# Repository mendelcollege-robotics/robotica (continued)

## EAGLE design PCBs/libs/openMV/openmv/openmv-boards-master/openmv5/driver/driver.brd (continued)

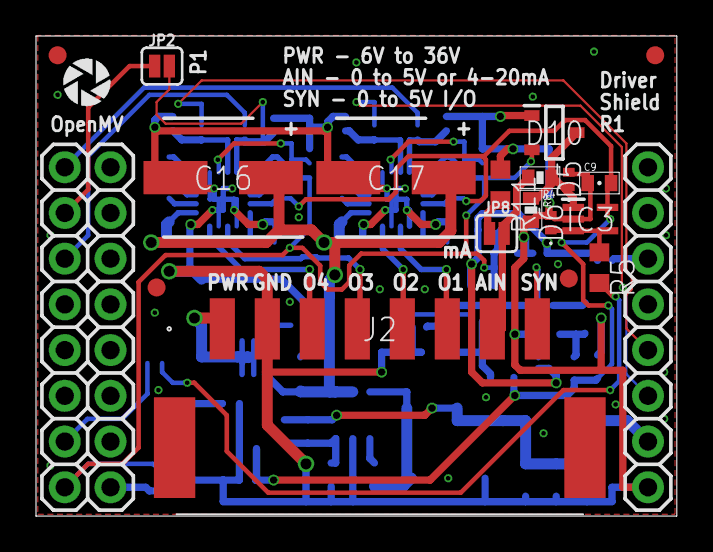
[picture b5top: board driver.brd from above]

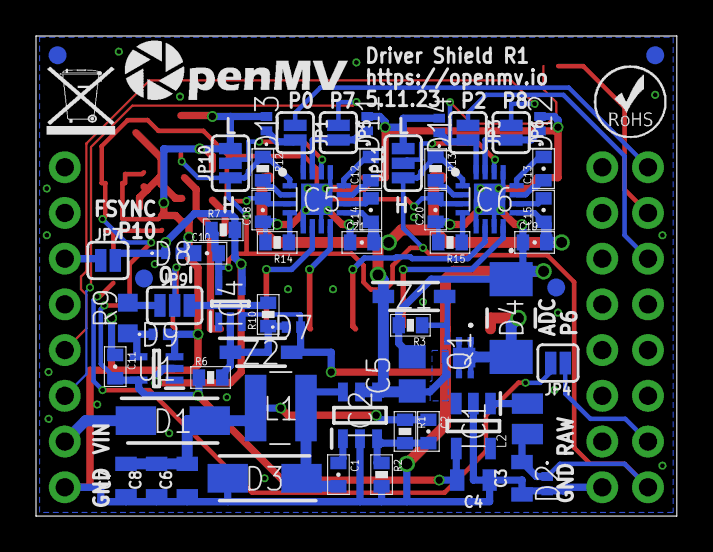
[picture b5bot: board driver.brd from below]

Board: 2 copper layers, 35.6 x 26.7 mm, 87 parts (67 on the bottom side), 50 nets.

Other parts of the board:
U$1: WEEE
U$2: ROHS
U$3: OMV-LOGO
U$9: OPENMV-LOGO

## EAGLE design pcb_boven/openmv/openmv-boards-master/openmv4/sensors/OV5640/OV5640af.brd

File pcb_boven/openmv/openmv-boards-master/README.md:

# OpenMV Boards

OpenMV boards, schematics, layouts, and CAD.

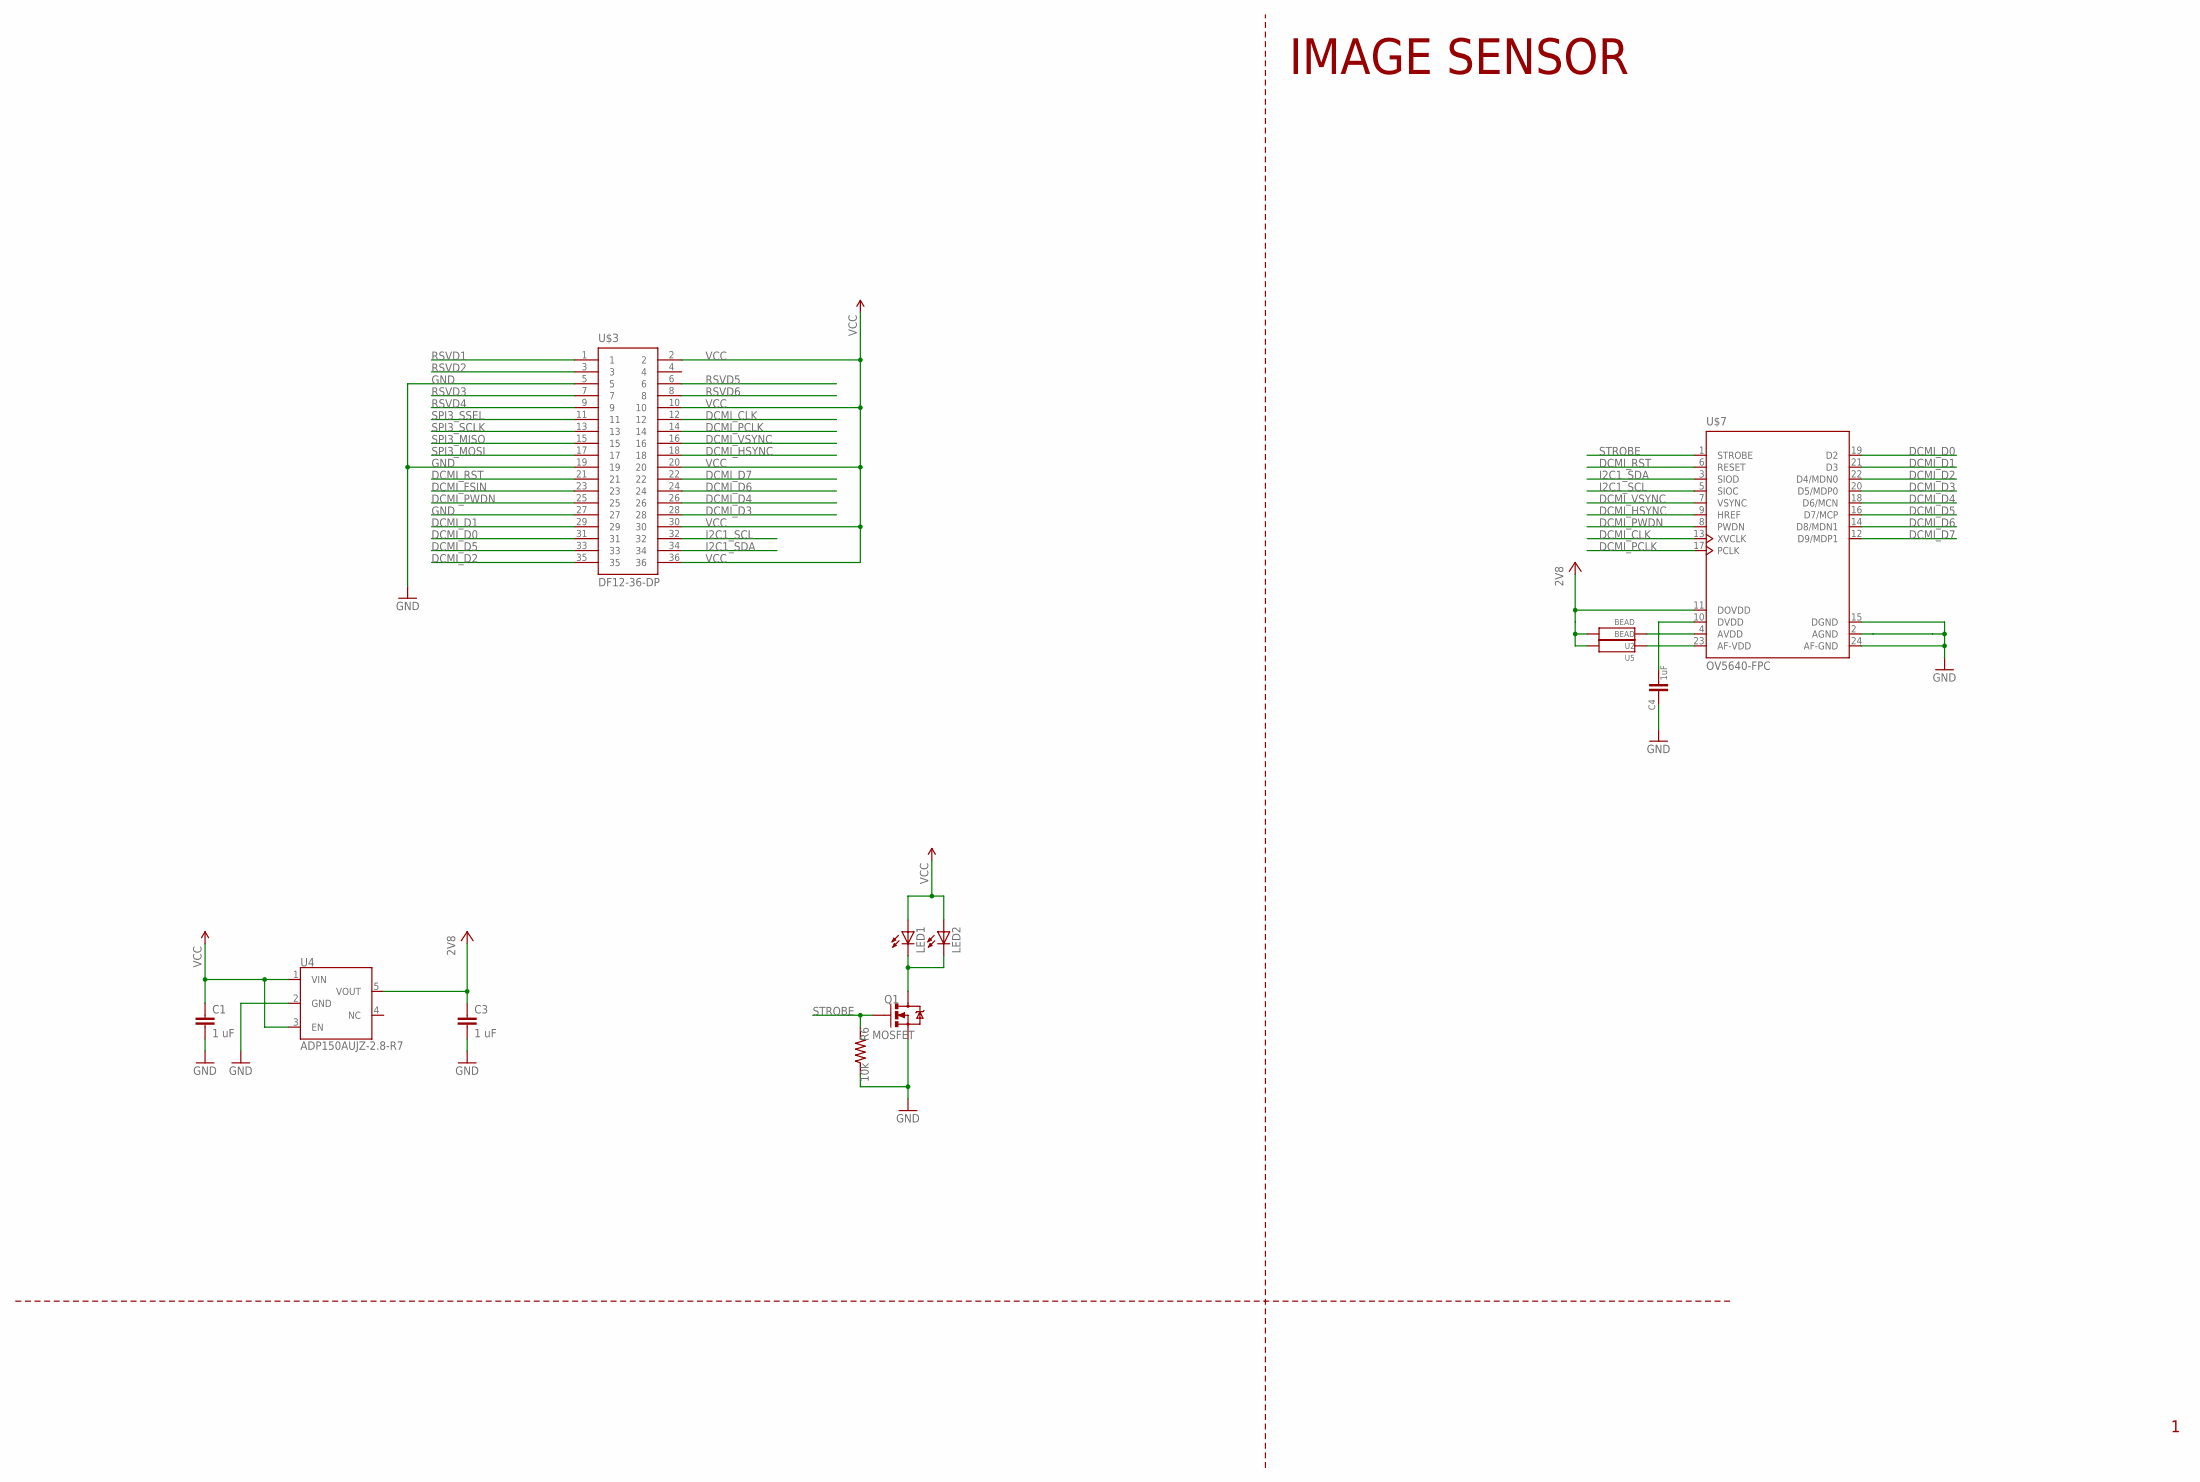
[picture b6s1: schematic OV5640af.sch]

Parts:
C1, C3: 1 uF; 0402-CAP
C4: 1uF; 0402-CAP
LED1, LED2: LEDCHIPLED_1206; CHIPLED_1206
Q1: MOSFET; SOT23-3
R6: 10k; 0603-RES
U2, U5: BEAD; 0402-CAP
U4: ADP150AUJZ-2.8-R7; SOT23-5
U$3: DF12-36-DP
U$7: OV5640-FPC; FPC24

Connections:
2V8: C3.1, U2.2, U4.5 (VOUT), U5.2, U$7.11 (DOVDD)
AF-VDD: U5.1, U$7.23 (AF-VDD)
AVDD: U2.1, U$7.4 (AVDD)
DCMI_CLK: U$3.12, U$7.13 (XVCLK)
DCMI_D0: U$3.31, U$7.19 (D2)
DCMI_D1: U$3.29, U$7.21 (D3)
DCMI_D2: U$3.35, U$7.22 (D4/MDN0)
DCMI_D3: U$3.28, U$7.20 (D5/MDP0)
DCMI_D4: U$3.26, U$7.18 (D6/MCN)
DCMI_D5: U$3.33, U$7.16 (D7/MCP)
DCMI_D6: U$3.24, U$7.14 (D8/MDN1)
DCMI_D7: U$3.22, U$7.12 (D9/MDP1)
DCMI_FSIN: U$3.23
DCMI_HSYNC: U$3.18, U$7.9 (HREF)
DCMI_PCLK: U$3.14, U$7.17 (PCLK)
DCMI_PWDN: U$3.25, U$7.8 (PWDN)
DCMI_RST: U$3.21, U$7.6 (RESET)
DCMI_VSYNC: U$3.16, U$7.7 (VSYNC)
DVDD: C4.1, U$7.10 (DVDD)
GND: C1.2, C3.2, C4.2, Q1.2 (S), R6.1, U4.2 (GND), U$3.5, U$3.19, U$3.27, U$7.2 (AGND), U$7.15 (DGND), U$7.24 (AF-GND)
I2C1_SCL: U$3.32, U$7.5 (SIOC)
I2C1_SDA: U$3.34, U$7.3 (SIOD)
LEDK: LED1.C, LED2.C, Q1.3 (D)
RSVD1: U$3.1
RSVD2: U$3.3
RSVD3: U$3.7
RSVD4: U$3.9
RSVD5: U$3.6
RSVD6: U$3.8
SPI3_MISO: U$3.15
SPI3_MOSI: U$3.17
SPI3_SCLK: U$3.13
SPI3_SSEL: U$3.11
STROBE: Q1.1 (G), R6.2, U$7.1 (STROBE)
VCC: C1.1, LED1.A, LED2.A, U4.1 (VIN), U4.3 (EN), U$3.2, U$3.10, U$3.20, U$3.30, U$3.36

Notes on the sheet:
IMAGE SENSOR

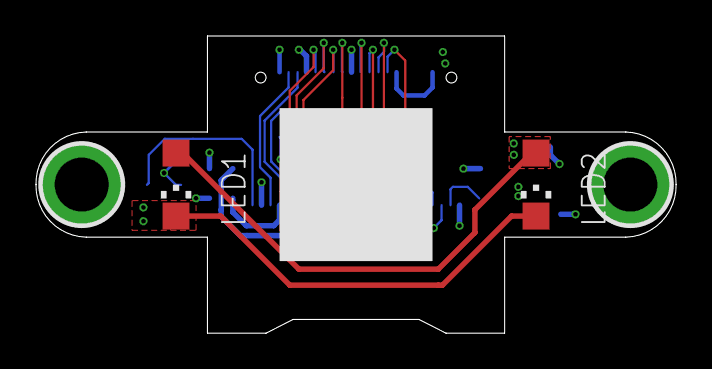
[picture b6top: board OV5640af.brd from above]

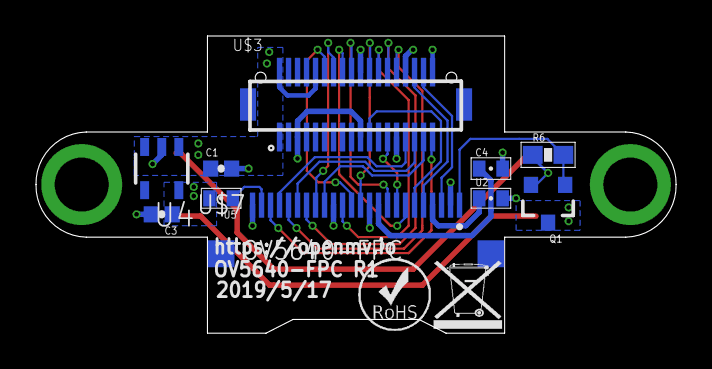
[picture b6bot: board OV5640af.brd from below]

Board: 4 copper layers, 35.6 x 16.5 mm, 14 parts (12 on the bottom side), 24 nets.

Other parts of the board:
U$1: WEEE
U$2: ROHS

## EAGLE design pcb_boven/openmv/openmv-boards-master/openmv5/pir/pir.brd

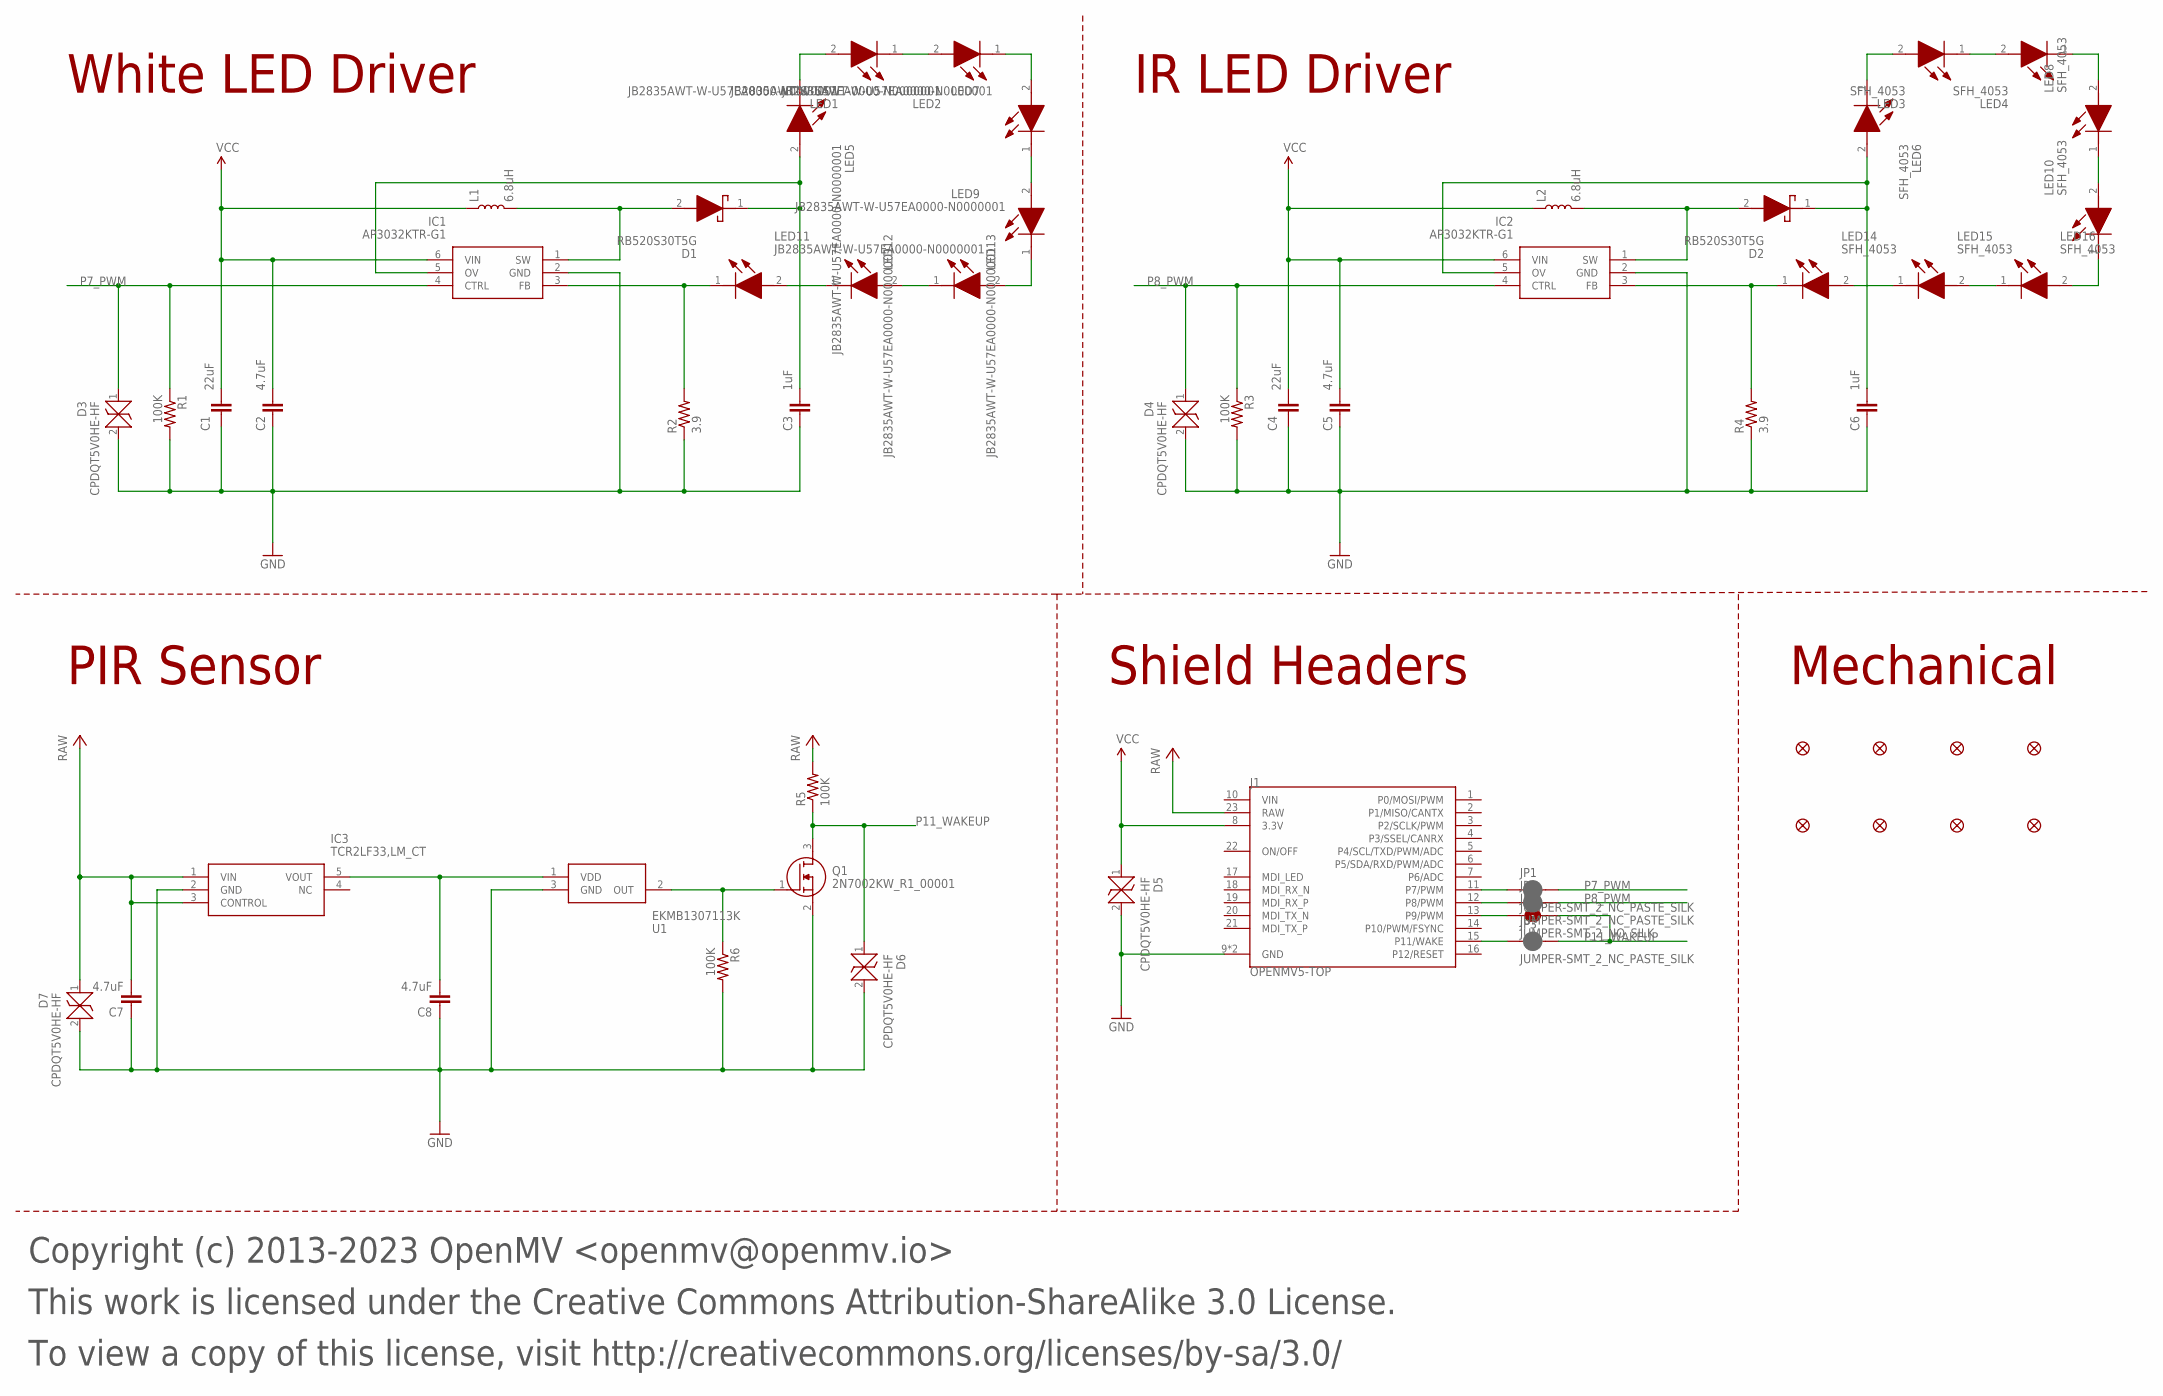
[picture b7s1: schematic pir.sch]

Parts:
C1, C4: 22uF; 0805; MPN CL21A226MQQNNNE
C2, C5, C7, C8: 4.7uF; 0402-CAP; MPN JMK105BBJ475MV-F
C3, C6: 1uF; 0402-CAP; MPN GRM155R6YA105KE11D
D1, D2: RB520S30T5G; SODFL1608X70N; MPN RB520S30T5G
D3, D4, D5, D6, D7: CPDQT5V0HE-HF; CPDQT5V0HEHF; MPN CPDQT5V0HE-HF
FD1, FD2, FD3, FD4, FD5, FD6, FD7, FD8: FIDUCIAL1X2; FIDUCIAL-1X2
IC1, IC2: AP3032KTR-G1; SOT95P280X145-6N; MPN AP3032KTR-G1
IC3: TCR2LF33,LM_CT; TCR2LF33LMCT; MPN TCR2LF33,LM(CT
J1: OPENMV5-TOP
JP1, JP2, JP3: JUMPER-SMT_2_NC_PASTE_SILK; SMT-JUMPER_2_NC_PASTE_SILK
JP4: JUMPER-SMT_2_NO_SILK; SMT-JUMPER_2_NO_SILK
L1, L2: 6.8uH; 0805; MPN MLZ2012M6R8WT000
LED1, LED2, LED5, LED7, LED9, LED11, LED12, LED13: JB2835AWT-W-U57EA0000-N0000001; JB2835AWTWU57EA0000N0000001; MPN JB2835AWT-W-U57EA0000-N0000001
LED3, LED4, LED6, LED8, LED10, LED14, LED15, LED16: SFH_4053; LEDC1005X55N; MPN SFH 4053
Q1: 2N7002KW_R1_00001; SOT65P210X110-3N; MPN 2N7002KW_R1_00001
R1, R3, R5, R6: 100K; 0402-RES; MPN AC0402FR-07100KL
R2, R4: 3.9; R2512; MPN 35203R9JT
U1: EKMB1307113K; EKMB1304111K; MPN EKMB1307113K

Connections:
GND: C1.1, C2.1, C3.1, C4.1, C5.1, C6.1, C7.1, C8.1, D3.2, D4.2, D5.2, D6.2, D7.2, IC1.2 (GND), IC2.2 (GND), IC3.2 (GND), J1.9 (GND), J1.24 (GND), Q1.2 (S), R1.2, R2.1, R3.2, R4.1, R6.2, U1.3 (GND)
I1: LED3.2 (A), LED6.1 (K)
I2: LED3.1 (K), LED4.2 (A)
I3: LED4.1 (K), LED8.2 (A)
I4: LED8.1 (K), LED10.2 (A)
I5: LED10.1 (K), LED16.2 (A)
I6: LED15.2 (A), LED16.1 (K)
I7: LED14.2 (A), LED15.1 (K)
IFB: IC2.3 (FB), LED14.1 (K), R4.2
IOV: C6.2, D2.1 (K), IC2.5 (OV), LED6.2 (A)
ISW: D2.2 (A), IC2.1 (SW), L2.2
OUT: Q1.1 (G), R6.1, U1.2 (OUT)
P7_PWM: D3.1, IC1.4 (CTRL), JP1.2, R1.1
P7_PWM_INT: J1.11 (P7/PWM), JP1.1
P8_PWM: D4.1, IC2.4 (CTRL), JP2.2, R3.1
P8_PWM_INT: J1.12 (P8/PWM), JP2.1
P11_WAKEUP: D6.1, JP3.2, JP4.2, Q1.3 (D), R5.1
P11_WAKEUP_INT: J1.15 (P11/WAKE), JP3.1
P11_WAKEUP_INT_2: J1.13 (P9/PWM), JP4.1
RAW: C7.2, D7.1, IC3.1 (VIN), IC3.3 (CONTROL), J1.23 (RAW), R5.2
VCC: C1.2, C2.2, C4.2, C5.2, D5.1, IC1.6 (VIN), IC2.6 (VIN), J1.8 (3.3V), L1.1, L2.1
VDD: C8.2, IC3.5 (VOUT), U1.1 (VDD)
W1: LED1.2 (A), LED5.1 (K)
W2: LED1.1 (K), LED2.2 (A)
W3: LED2.1 (K), LED7.2 (A)
W4: LED7.1 (K), LED9.2 (A)
W5: LED9.1 (K), LED13.2 (A)
W6: LED12.2 (A), LED13.1 (K)
W7: LED11.2 (A), LED12.1 (K)
WFB: IC1.3 (FB), LED11.1 (K), R2.2
WOV: C3.2, D1.1 (K), IC1.5 (OV), LED5.2 (A)
WSW: D1.2 (A), IC1.1 (SW), L1.2

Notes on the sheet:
Copyright (c) 2013-2023 OpenMV <openmv@openmv.io>
This work is licensed under the Creative Commons Attribution-ShareAlike 3.0 License.
To view a copy of this license, visit http://creativecommons.org/licenses/by-sa/3.0/
White LED Driver
PIR Sensor
Mechanical
IR LED Driver
Shield Headers

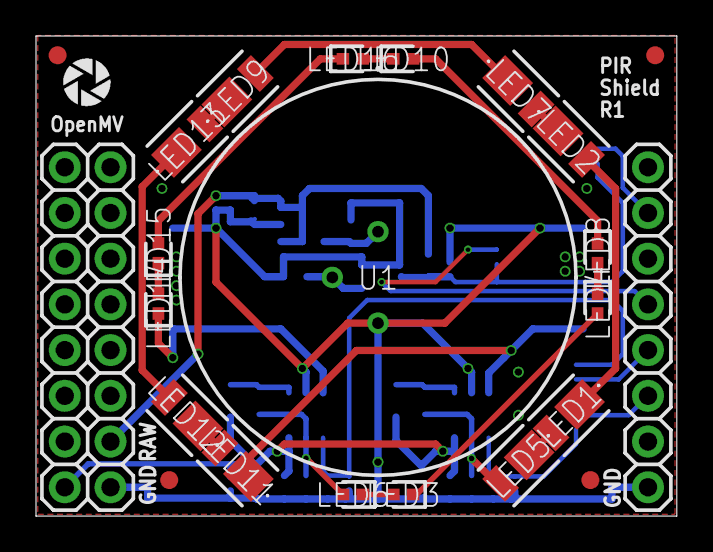
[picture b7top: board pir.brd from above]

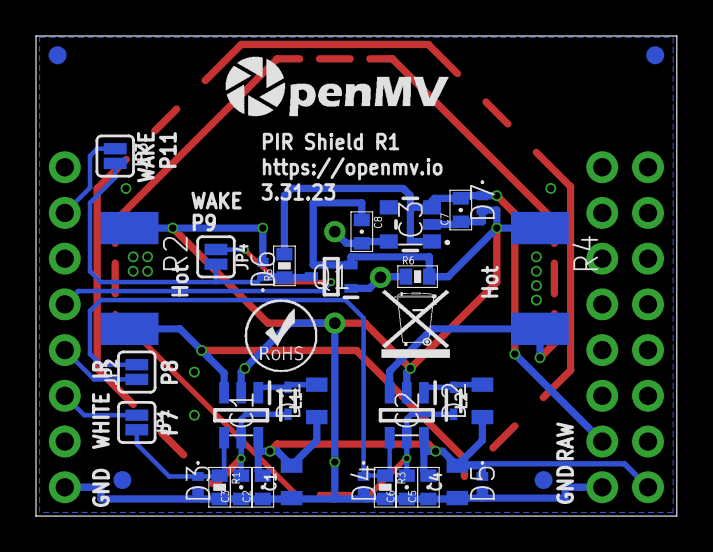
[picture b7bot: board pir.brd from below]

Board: 2 copper layers, 35.6 x 26.7 mm, 61 parts (38 on the bottom side), 32 nets.

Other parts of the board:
U$1: WEEE
U$2: ROHS
U$3: OMV-LOGO
U$9: OPENMV-LOGO

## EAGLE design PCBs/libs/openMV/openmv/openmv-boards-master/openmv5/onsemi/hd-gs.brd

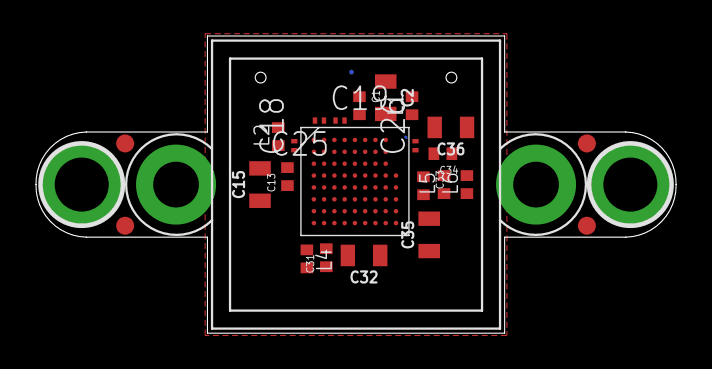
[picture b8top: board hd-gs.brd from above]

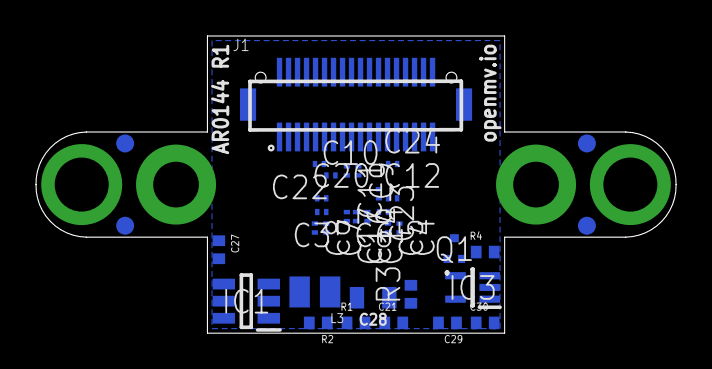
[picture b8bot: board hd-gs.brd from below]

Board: 6 copper layers, 35.6 x 16.5 mm, 60 parts (35 on the bottom side), 36 nets.

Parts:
C1, C13, C27, C29, C30, C31, C33, C34: 4.7uF; 0402
C2, C15, C28, C32, C35, C36: 22uF; 0805
C3, C4, C5, C6, C7, C8, C9, C10, C11, C12, C14, C16, C17, C18, C19, C20, C22, C23, C24, C25, C26: 0.22uF; C0201
C21: 6.8pF; 0402
FD1, FD2, FD3, FD4, FD5, FD6, FD7, FD8: FIDUCIAL1X2; FIDUCIAL-1X2
H1: LENSMOUNT20MM; LENSMOUNT-20MM
IC1: TLV62568PDDCR; SOT95P280X110-6N
IC2: AR0144CSSC20SUKA0
IC3: MIC5365-2.8YC5-TR; SOT65P210X110-5N
J1: DF12-36-DP
L1, L2, L4, L5, L6: 100; 0402
L3: MAKK2016T2R2M; INDC2016X100N
Q1: SSM3J15FV,L3F; SSM3J15FVL3F
R1, R2, R4: 100K; R0402
R3: 10K; R0402

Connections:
DCMI_CLK: IC2.P$11, J1.12
DCMI_D0: IC2.P$47, J1.3
DCMI_D1: IC2.P$46, J1.1
DCMI_D2: IC2.P$45, J1.9
DCMI_D3: IC2.P$38, J1.7
DCMI_D4: IC2.P$37, J1.31
DCMI_D5: IC2.P$34, J1.29
DCMI_D6: IC2.P$35, J1.35
DCMI_D7: IC2.P$25, J1.28
DCMI_D8: IC2.P$26, J1.26
DCMI_D9: IC2.P$27, J1.33
DCMI_D10: IC2.P$28, J1.24
DCMI_D11: IC2.P$17, J1.22
DCMI_FSIN: IC2.P$40, J1.23
DCMI_HSYNC: IC2.P$9, J1.18
DCMI_PCLK: IC2.P$19, J1.14
DCMI_PWDN: J1.25, Q1.1
DCMI_PWDN_INT: IC3.3, Q1.3, R4.1
DCMI_RST: J1.21, R3.2
DCMI_SCL: IC2.P$23, J1.32
DCMI_SDA: IC2.P$39, J1.34
DCMI_VSYNC: IC2.P$20, J1.16
FB: C21.2, IC1.6, R1.1, R2.1
GND: C1.1, C2.1, C3.2, C4.2, C5.2, C6.2, C7.2, C8.2, C9.2, C10.2, C11.2, C12.2, C13.1, C14.2, C15.1, C16.2, C17.2, C18.2, C19.2, C20.2, C22.2, C23.2, C24.2, C25.2, C26.2, C27.1, C28.1, C29.1, C30.1, C31.1, C32.1, C33.1, C34.1, C35.1, C36.1, IC1.2, IC2.P$1, IC2.P$8, IC2.P$15, IC2.P$29, IC2.P$30, IC2.P$31, IC2.P$33, IC2.P$41, IC2.P$43, IC2.P$49, IC2.P$50, IC2.P$54, IC2.P$58, IC2.P$63, IC2.P$64, IC2.P$65, IC2.P$66, IC2.P$67, IC3.2, J1.5, J1.6, J1.8, J1.19, J1.27, R2.2, R4.2
RESET_N: IC1.5, IC2.P$52, R3.1
SPI_MISO: IC2.P$48, J1.15
SW: IC1.3, L3.2
VAA: C3.1, C4.1, C5.1, C6.1, C7.1, C8.1, C31.2, C32.2, IC2.P$53, IC2.P$59, IC2.P$61, IC2.P$62, IC2.P$68, IC2.P$69, L4.1
VAA_PIX: C20.1, C33.2, C35.2, IC2.P$51, L5.1
VCC: C27.2, IC1.4, J1.2, J1.10, J1.20, J1.30, J1.36
VDD: C1.2, C2.2, C10.1, C11.1, C12.1, C14.1, C16.1, C17.1, C18.1, C19.1, IC2.P$3, IC2.P$10, IC2.P$22, IC2.P$32, IC2.P$44, IC2.P$55, IC2.P$56, IC2.P$57, L1.1
VDDA: C30.2, IC3.1, J1.4, Q1.2
VDDIO: C22.1, C23.1, C24.1, C25.1, C26.1, C34.2, C36.2, IC2.P$2, IC2.P$16, IC2.P$18, IC2.P$24, IC2.P$36, L6.1
VDDIO_REG: C29.2, IC1.1, IC3.5, L4.2, L5.2, L6.2
VDD_PHY: C9.1, C13.2, C15.2, IC2.P$21, L2.1
VDD_REG: C21.1, C28.2, L1.2, L2.2, L3.1, R1.2

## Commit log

2022-12-08 full half or no
2022-12-08 fouths
2022-12-08 eights
2022-12-08 Update LICENSE
2022-12-08 didvthing
2024-04-29 add buz
2024-04-29 buzz debug
2024-04-30 Create l
2024-04-30 Update and rename pcb/l to pcb_readme
2024-05-03 Commit message
2024-05-04 pcb boven gemaakt
2024-05-04 pcb onder gemaakt
2024-06-02 add files
2024-06-03 add connect between teensy and openmv
2024-06-03 update com
2024-06-05 add mcp
2024-06-05 add mcu
2024-06-09 Create e
2024-06-09 upd pcb
2024-06-09 manifacture
2024-06-09 pcb_onder y
2024-06-10 add CODE
2024-06-10 code
2024-06-11 3d file pcb
2024-06-11 lower_pcb
2024-06-12 add_3d
2024-06-14 dfas
2024-06-15 4dip
2024-06-20 poster
2024-06-20 dsfa
2024-06-21 post
2024-06-21 poster readme weird fix
2024-06-22 update repo structure update poster add code flowchart
2024-06-22 remove OLD update poster
2024-06-23 git structure change poster
2024-06-24 lower pcb
2024-06-25 3d file of pcb
2024-06-26 part diagram
2024-06-30 motor drivers
2024-06-30 to fix: change mcp2.analogWrite(m1pwm1, spdA); to us softPWM
2024-07-03 soft PWM added
2024-07-03 direction code and better IR seeker code
2024-07-06 Motor Calibration capabilities
2024-07-07 Motor driver code complette need to test/fix MCP23017
2024-07-07 setting 1 complete need to do 2, 3, 4
2024-07-16 maini code
2024-07-22 change folder struct
2024-07-27 PCB schemas
2024-08-27 add full pcb schema
2024-09-05 nog lang niet klaar.
2024-09-05 update pcb led
2024-10-06 dfgs
2024-10-07 Onder pcb kan gemaakt worden
    De rest moet nog uitgewerkt worden
2024-10-07 Onder pcb kan gemaakt worden
2024-10-08 ONDERPCB
2024-10-08 UPDATE FOLDER STUCTURE
    MOET APARTE_PCB NOG VERWIJDERTEN WINDOWS HEEFT BEST VERGRENDELD
2024-10-13 Rename 3dfiles/Robotica Volledige Robot3 v5.f3z to 3dfiles/backups/Robotica Volledige Robot3 v5.f3z
2024-10-14 laaste boutjes
2024-10-14 Rename 3dfiles/Robotica Volledige Robot3 v11.f3z to 3dfiles/backups/Robotica Volledige Robot3 v11.f3z
2024-10-14 kleine aanpassing op vorige aanpassingen
2024-10-14 Rename 3dfiles/Robotica Volledige Robot3 v13.f3z to 3dfiles/backups/Robotica Volledige Robot3 v13.f3z
2024-10-17 pcb's
2024-10-18 midden bijna klaar
2024-10-18 alleen solinoid nog
2024-10-19 solenoid gaten
2024-10-19 Rename 3dfiles/Robotica Volledige Robot3 v15.f3z to 3dfiles/backups/Robotica Volledige Robot3 v15.f3z
2024-10-19 Rename 3dfiles/Robotica Volledige Robot3 v15.stl to 3dfiles/backups/Robotica Volledige Robot3 v15.stl
2024-10-19 kicker
2024-10-30 Create Onder pcb bijna af
2024-10-30 asedfdgasfsdgfvdfgasdfgbs
2024-11-01 schroef geaard
    moet nog onderste schroef
2024-11-04 Rename 3dfiles/Robotica Volledige Robot3 v16.f3z to 3dfiles/backups/Robotica Volledige Robot3 v16.f3z
2024-11-04 Rename 3dfiles/Robotica Volledige Robot3 v16.stl to 3dfiles/backups/Robotica Volledige Robot3 v16.stl
2024-11-04 Rename 3dfiles/Robotica Volledige Robot3 v17.f3z to 3dfiles/backups/Robotica Volledige Robot3 v17.f3z
2024-11-04 Rename 3dfiles/Robotica Volledige Robot3 v17.stl to 3dfiles/backups/Robotica Volledige Robot3 v17.stl
2024-11-06 pcb pre autoroute upload
2024-11-06 Onderste mesh veranderd
2024-11-06 Rename 3dfiles/Robotica Volledige Robot3 v18.f3z to 3dfiles/backups/Robotica Volledige Robot3 v18.f3z
2024-11-06 Rename 3dfiles/Robotica Volledige Robot3 v18.stl to 3dfiles/backups/Robotica Volledige Robot3 v18.stl
2024-11-07 7-11
2024-11-07 af ready to check
2024-11-08 dgsrf
2024-12-19 Create verbeterde code door chatgpt
    ik heb de code in chat gestopt en heeft mij dit terug geschreven, kunnen we hier iets mee?
2025-02-06 halloi test
2025-03-20 things
2025-03-20 EEASFEESDFASDF
2025-03-20 send messages via serial
2025-03-20 able to convert ir signal into degrees
2025-03-20 issue 15 should be fixed
2025-03-20 color
2025-03-20 PWM with motors
2025-03-20 test
2025-03-21 fix serial
2025-03-21 fix PWM
2025-03-23 updated repo structure
2025-03-23 softpwm
2025-03-23 serial
2025-03-24 added git ignore files and removed .lck files
2025-03-26 Rename 3dfiles/soccerfield.obj to 3dfiles/oud/soccerfield.obj
2025-03-26 Rename 3dfiles/PCBboven.3mf to 3dfiles/oud/PCBboven.3mf
2025-03-26 Rename 3dfiles/PCBmidden.stl to 3dfiles/oud/PCBmidden.stl
2025-03-26 Rename 3dfiles/PCBonder.3mf to 3dfiles/oud/PCBonder.3mf
2025-03-26 Rename 3dfiles/PCBondermesh.3mf to 3dfiles/oud/PCBondermesh.3mf
2025-03-26 Rename 3dfiles/PCBondermesh.stl to 3dfiles/oud/PCBondermesh.stl
2025-03-26 Rename 3dfiles/feld.20240723-125216.FCBak to 3dfiles/oud/feld.20240723-125216.FCBak
2025-03-26 Rename 3dfiles/feld.FCStd to 3dfiles/oud/feld.FCStd
2025-03-26 Rename 3dfiles/onderpcb(new).dxf to 3dfiles/oud/onderpcb(new).dxf
2025-03-26 Rename 3dfiles/pcb_onder(oud).dxf to 3dfiles/oud/pcb_onder(oud).dxf
2025-03-26 Rename 3dfiles/pcb_midden(onderste_face).dxf to 3dfiles/oud/pcb_midden(onderste_face).dxf
2025-03-26 Rename 3dfiles/pcb_midden(bovenste_face).dxf to 3dfiles/oud/pcb_midden(bovenste_face).dxf
2025-03-26 Rename 3dfiles/pcb_boven.dxf to 3dfiles/oud/pcb_boven.dxf
2025-03-26 Rename 3dfiles/Robot V3.1 concept v3.f3z to 3dfiles/oud/Robot V3.1 concept v3.f3z
2025-03-26 Rename 3dfiles/Robotica Volledige Robot3 v29.f3z to 3dfiles/oud/Robotica Volledige Robot3 v29.f3z
2025-03-26 Rename 3dfiles/Robotica Volledige Robot3 v29.stl to 3dfiles/oud/Robotica Volledige Robot3 v29.stl
2025-03-27 oude shit
2025-04-01 did a lot of thing lately
2025-04-06 nuttige bronnen om te leren
2025-04-06 test sign key
    Multi-line description of commit,
    feel free to be detailed.
2025-04-06 foto robot (poster?)
2025-04-24 sim for omni drive
2025-05-07 ksdbks
2025-05-08 test sign live usb
2025-05-08 paar best vergeten
2025-05-11 added encoder again
    Multi-line description of commit,
    feel free to be detailed.
2025-05-12 cam comm + readme -4
    Multi-line description of commit,
    feel free to be detailed.
2025-05-22 create issue templates
2025-11-14 INITIAL commit
    mosrtly the bottom pcb
2025-11-14 test
    test
2025-11-14 begin pcb total
2025-11-15 power toegevoegd
2025-11-15 V1.01
2025-11-17 pcb changes
    -file now in electronics
    -motordriver integraded
    -etc
2025-11-20 -motor driver -imu !!!need to check logic level converters!!!
2025-11-20 pinnen toegevoegd en goede eps32
2025-11-20 begin boven PCB
2025-11-20 boven pcb best ver af
2025-11-20 alleen nog cxampera
2025-11-21 some final adjustments.
2025-11-21 boven pcb af
2025-11-21 M1 is af
2025-11-21 fsdgal;nk
2025-11-28 V1.1
2025-12-02 motor driver symbol changed
2026-02-08 SOFTPWM
    Multi-line description of commit,
    feel free to be detailed.
    [Issue: X]
2026-02-08 debug message)
    Multi-line description of commit,
    feel free to be detailed.
    [Issue: X]
2026-02-08 created PID and it better fucking works
    Multi-line description of commit,
    feel free to be detailed.
    [Issue: X]
2026-02-08 im a idiot
    had m1encSP to < 0 give error but a motor can also be not moving no < 0 so
2026-02-08 i am the only one who reads there anyways so why do i bother
    imagen there is a butifull commit message here
    _____________________________________
    / Nothing so needs reforming as other \
    | people's habits. |
    | |
    \ -- Mark Twain /
2026-02-08 why does github say unverified
    added single empy line
    [Issue: X]
2026-02-08 im bored
    _____________________________
    < Avoid reality at all costs. >
    -----------------------------
    \
    \
    /\_)o<
